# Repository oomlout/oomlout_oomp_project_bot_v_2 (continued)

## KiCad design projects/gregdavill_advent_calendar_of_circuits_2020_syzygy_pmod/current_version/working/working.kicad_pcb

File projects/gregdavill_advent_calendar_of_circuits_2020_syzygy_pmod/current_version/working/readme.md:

# advent_calendar_of_circuits_2020
 
## summary 
* id: gregdavill_advent_calendar_of_circuits_2020_syzygy_pmod
* user: gregdavill
* name: advent_calendar_of_circuits_2020
* board: syzygy_pmod
* repo: https://github.com/gregdavill/advent-calendar-of-circuits-2020
* src_file_repo_kicad_pcb: syzygy-pmod/kicad-src/syzygy-pmod.kicad_pcb
* src_file_repo_kicad_pcb_link: https://github.com/gregdavill/advent-calendar-of-circuits-2020/tree/main/syzygy-pmod/kicad-src/syzygy-pmod.kicad_pcb
* src_file_repo_kicad_sch: syzygy-pmod/kicad-src/p-mcu.kicad_sch
* src_file_repo_kicad_sch_link: https://github.com/gregdavill/advent-calendar-of-circuits-2020/tree/main/syzygy-pmod/kicad-src/p-mcu.kicad_sch

* src_file_repo_sch: 
* src_file_repo_sch_link: https://github.com/gregdavill/advent-calendar-of-circuits-2020/tree/main/
* full details link: https://github.com/oomlout/oomlout_oomp_project_bot_v_2/tree/main/projects/gregdavill_advent_calendar_of_circuits_2020_syzygy_pmod/current_version/working

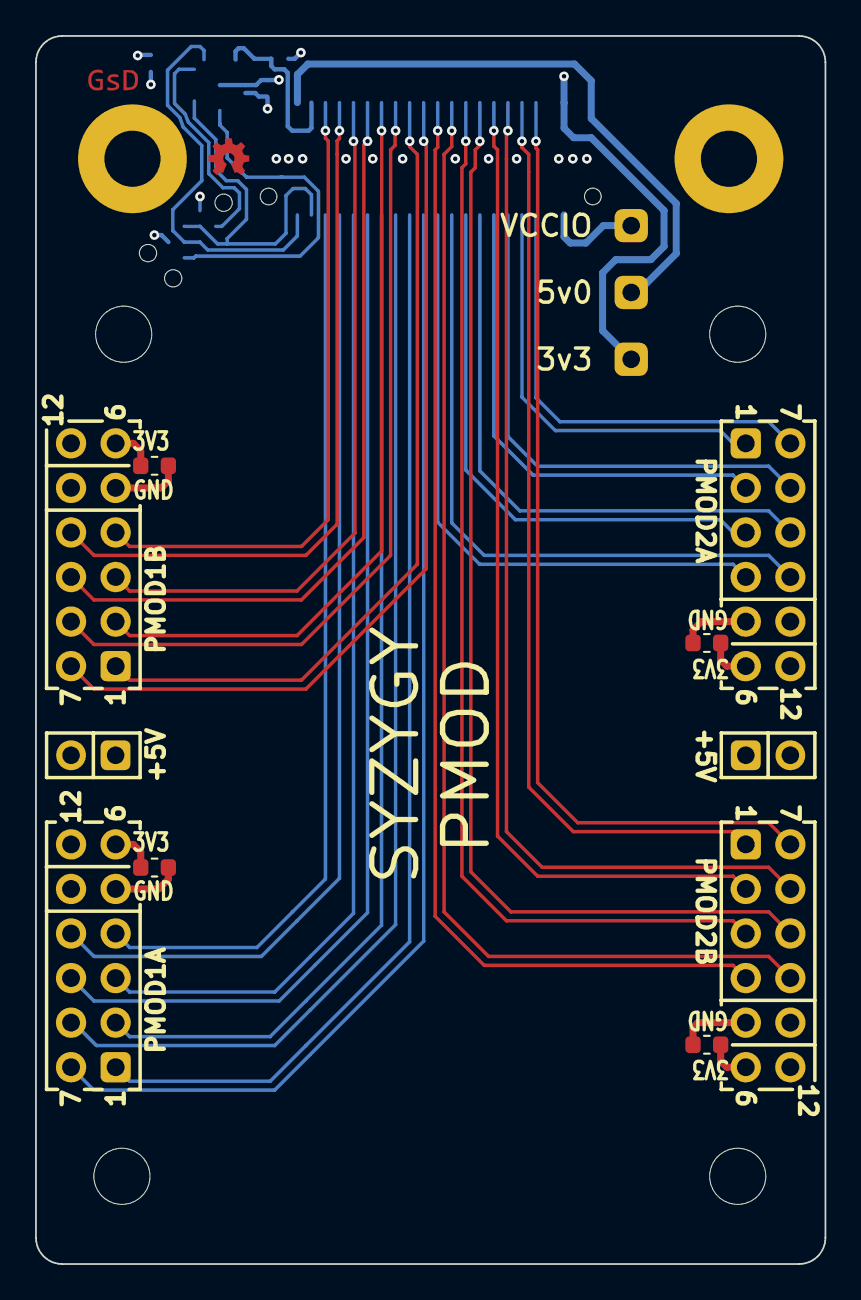
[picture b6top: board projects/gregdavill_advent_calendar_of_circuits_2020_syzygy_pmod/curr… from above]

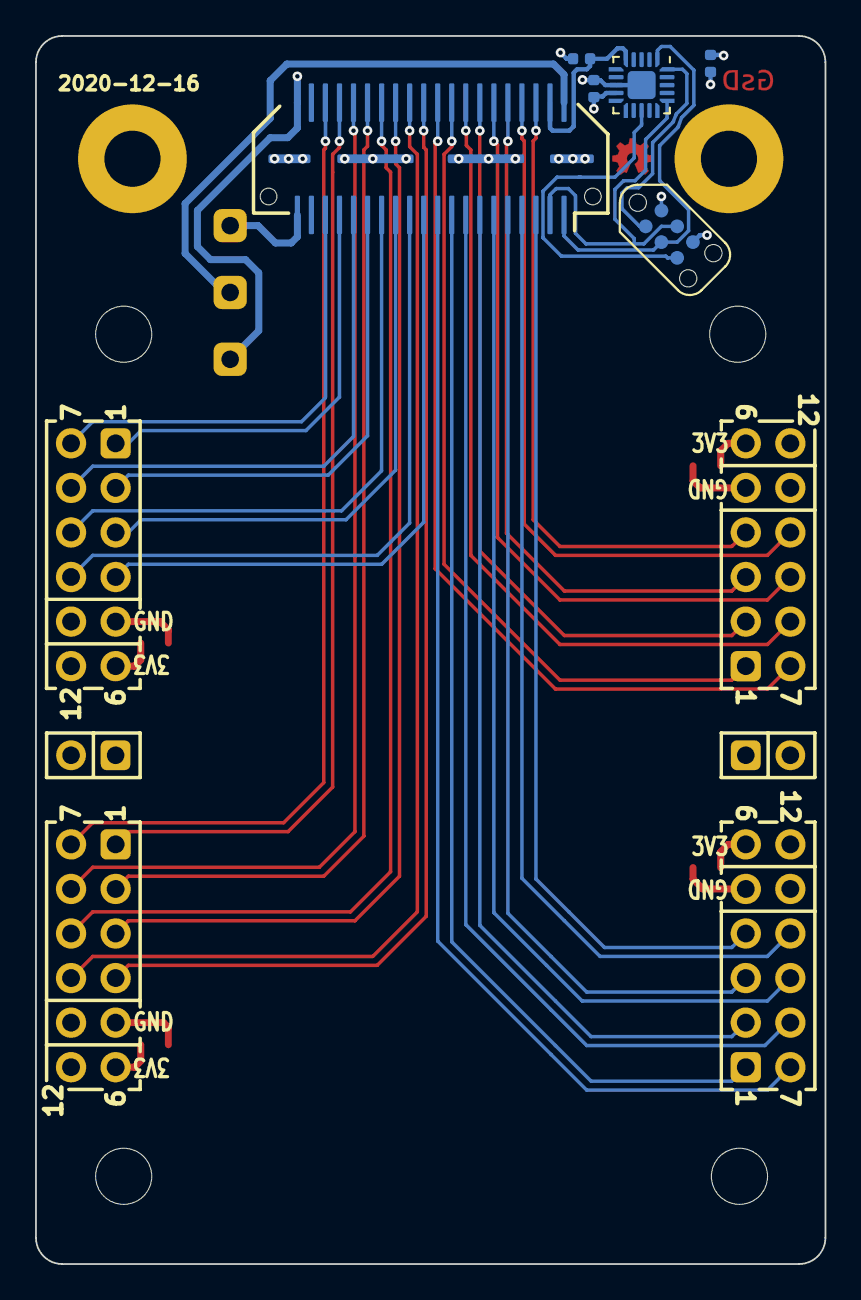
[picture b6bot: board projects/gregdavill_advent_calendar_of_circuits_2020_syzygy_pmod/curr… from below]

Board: 4 copper layers, 45.0 x 70.0 mm, 23 parts (6 on the bottom side), 41 nets.

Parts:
C1, C2, C3, C4: DNP; C_0603_1608Metric
C9: 0.1uF; C_0402_1005Metric
C10: 1uF; C_0402_1005Metric
H1, H2, H3, H4: MountingHole; MountingHole_3.2mm_M3_DIN965
J1: SYZYGY-STD; SYZYGY-STD-POD
J2, J8, J9, J11: PMOD; PMOD_Angled_2x06
J3: TagConnect; TC2030-NL_SMALL
J4, J5, J6: Conn_01x01_Male; PinHeader_1x01_P2.54mm_Vertical
J7, J10: 5V AUX; PinHeader_2x01_P2.54mm_Vertical
R15: 10K; R_0402_1005Metric
U2: ATtiny44A-MMH; QFN-20-1EP_3x3mm_P0.45mm_EP1.6x1.6mm

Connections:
+3V3: C1.2, C2.2, C3.2, C4.2, C9.1, C10.1, J1.40 (+3.3V), J2.6, J2.12, J3.2, J5.1, J8.6, J8.12, J9.6, J9.12, J11.6, J11.12, R15.1, U2.9 (VCC)
+5V: J1.2 (+5V), J4.1, J7.1, J10.1
/P1A1: J1.17 (S12_D6P), J9.1
/P1A2: J1.13 (S8_D4P), J9.2
/P1A3: J1.9 (S4_D2P), J9.3
/P1A4: J1.5 (S0_D0P), J9.4
/P1A7: J1.19 (S14_D6N), J9.7
/P1A8: J1.15 (S10_D4N), J9.8
/P1A9: J1.11 (S6_D2N), J9.9
/P1A10: J1.7 (S2_D0N), J9.10
/P1B1: J1.18 (S13_D7P), J11.1
/P1B2: J1.14 (S9_D5P), J11.2
/P1B3: J1.10 (S5_D3P), J11.3
/P1B4: J1.6 (S1_D1P), J11.4
/P1B7: J1.20 (S15_D7N), J11.7
/P1B8: J1.16 (S11_D5N), J11.8
/P1B9: J1.12 (S7_D3N), J11.9
/P1B10: J1.8 (S3_D1N), J11.10
/P2A1: J1.33 (P2C_CLKP), J2.1
/P2A2: J1.29 (S24), J2.2
/P2A3: J1.25 (S20), J2.3
/P2A4: J1.21 (S16), J2.4
/P2A7: J1.35 (P2C_CLKN), J2.7
/P2A8: J1.31 (S26), J2.8
/P2A9: J1.27 (S22), J2.9
/P2A10: J1.23 (S18), J2.10
/P2B1: J1.34 (C2P_CLKP), J8.1
/P2B2: J1.30 (S25), J8.2
/P2B3: J1.26 (S21), J8.3
/P2B4: J1.22 (S17), J8.4
/P2B7: J1.36 (C2P_CLKN), J8.7
/P2B8: J1.32 (S27), J8.8
/P2B9: J1.28 (S23), J8.9
/P2B10: J1.24 (S19), J8.10
/Peripheral MCU/MISO: J3.1, U2.20 (PA5)
/Peripheral MCU/~RESET: J3.5, U2.13 (~RESET~/PB3)
/RGA: J1.4 (R_GA), R15.2, U2.5 (AREF/PA0)
/SCL: J1.1 (SCL), J3.3, U2.1 (PA4)
/SDA: J1.3 (SDA), J3.4, U2.16 (PA6)
/VCCIO: J1.39 (VIO1), J6.1
GND: C1.1, C2.1, C3.1, C4.1, C9.2, C10.2, J1.41 (GND), J2.5, J2.11, J3.6, J7.2, J8.5, J8.11, J9.5, J9.11, J10.2, J11.5, J11.11, U2.8 (GND), U2.21 (GND)

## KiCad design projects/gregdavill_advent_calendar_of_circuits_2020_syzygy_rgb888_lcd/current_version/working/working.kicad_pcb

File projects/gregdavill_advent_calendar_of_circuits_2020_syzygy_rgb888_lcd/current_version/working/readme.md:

# advent_calendar_of_circuits_2020
 
## summary 
* id: gregdavill_advent_calendar_of_circuits_2020_syzygy_rgb888_lcd
* user: gregdavill
* name: advent_calendar_of_circuits_2020
* board: syzygy_rgb888_lcd
* repo: https://github.com/gregdavill/advent-calendar-of-circuits-2020
* src_file_repo_kicad_pcb: syzygy-rgb888-lcd/kicad-src/syzygy-rgb888-lcd.kicad_pcb
* src_file_repo_kicad_pcb_link: https://github.com/gregdavill/advent-calendar-of-circuits-2020/tree/main/syzygy-rgb888-lcd/kicad-src/syzygy-rgb888-lcd.kicad_pcb
* src_file_repo_kicad_sch: syzygy-rgb888-lcd/kicad-src/p-mcu.kicad_sch
* src_file_repo_kicad_sch_link: https://github.com/gregdavill/advent-calendar-of-circuits-2020/tree/main/syzygy-rgb888-lcd/kicad-src/p-mcu.kicad_sch

* src_file_repo_sch: 
* src_file_repo_sch_link: https://github.com/gregdavill/advent-calendar-of-circuits-2020/tree/main/
* full details link: https://github.com/oomlout/oomlout_oomp_project_bot_v_2/tree/main/projects/gregdavill_advent_calendar_of_circuits_2020_syzygy_rgb888_lcd/current_version/working

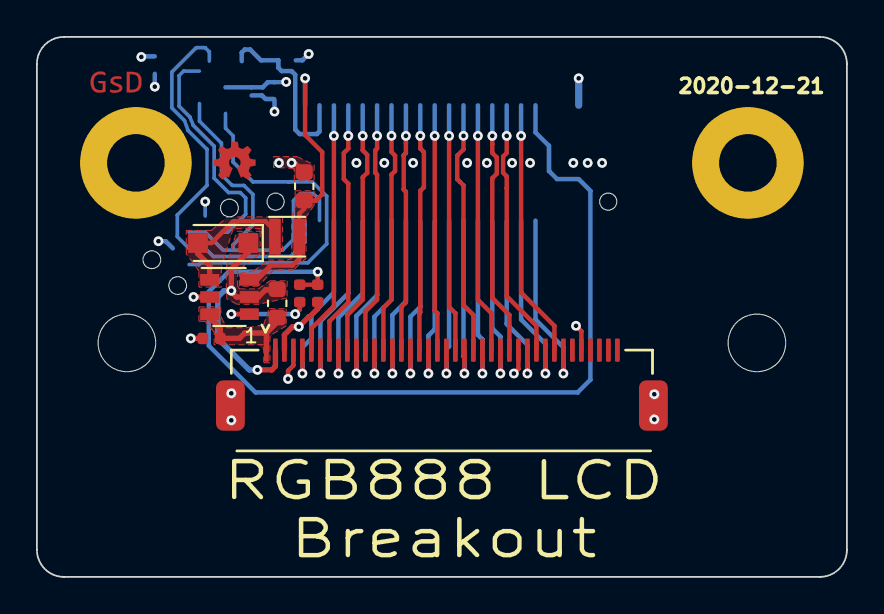
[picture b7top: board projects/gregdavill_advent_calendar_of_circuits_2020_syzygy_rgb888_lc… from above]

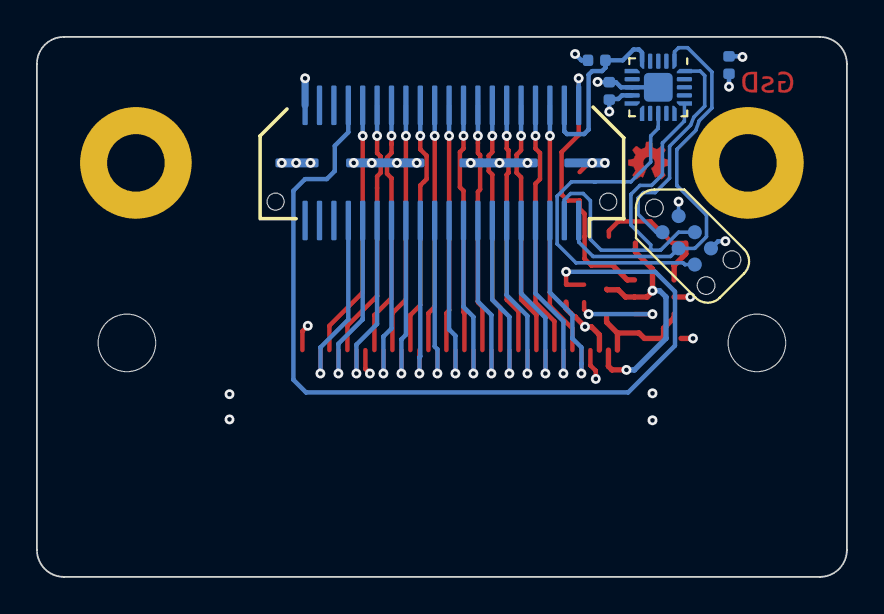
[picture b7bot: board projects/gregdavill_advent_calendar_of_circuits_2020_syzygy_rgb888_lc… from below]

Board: 4 copper layers, 45.0 x 30.0 mm, 17 parts (6 on the bottom side), 42 nets.

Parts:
C1: 0.1uF; C_0603_1608Metric
C2: 22uF; C_0603_1608Metric
C9: 0.1uF; C_0402_1005Metric
C10: 1uF; C_0402_1005Metric
D1: D_ALT; D_SOD-123F
H1, H2: MountingHole; MountingHole_3.2mm_M3_DIN965
J1: SYZYGY-STD; SYZYGY-STD-POD
J2: Conn_01x40_MountingPin; X05A20H40G
J3: TagConnect; TC2030-NL_SMALL
L1: 2.2uH; L_Taiyo-Yuden_MD-2020
R1: 1k; R_0402_1005Metric
R2: 10k; R_0402_1005Metric
R3: 5R1; R_0402_1005Metric
R15: 10K; R_0402_1005Metric
U1: PT4103; SOT-23-6
U2: ATtiny44A-MMH; QFN-20-1EP_3x3mm_P0.45mm_EP1.6x1.6mm

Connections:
+3V3: C9.1, C10.1, J1.40 (+3.3V), J2.4, J3.2, R15.1, U2.9 (VCC)
+5V: C2.1, J1.2 (+5V), L1.1, U1.6 (VIN)
/B0: J1.21 (S16), J2.21
/B1: J1.22 (S17), J2.22
/B2: J1.23 (S18), J2.23
/B3: J1.24 (S19), J2.24
/B4: J1.25 (S20), J2.25
/B5: J1.26 (S21), J2.26
/B6: J1.27 (S22), J2.27
/B7: J1.28 (S23), J2.28
/BLEN: J1.34 (C2P_CLKP), R1.1, R2.2
/CLK: J1.29 (S24), J2.30
/DEN: J1.33 (P2C_CLKP), J2.34
/DISP: J1.30 (S25), J2.31
/G0: J1.13 (S8_D4P), J2.13
/G1: J1.14 (S9_D5P), J2.14
/G2: J1.15 (S10_D4N), J2.15
/G3: J1.16 (S11_D5N), J2.16
/G4: J1.17 (S12_D6P), J2.17
/G5: J1.18 (S13_D7P), J2.18
/G6: J1.19 (S14_D6N), J2.19
/G7: J1.20 (S15_D7N), J2.20
/HSYNC: J1.31 (S26), J2.32
/Peripheral MCU/MISO: J3.1, U2.20 (PA5)
/Peripheral MCU/~RESET: J3.5, U2.13 (~RESET~/PB3)
/R0: J1.5 (S0_D0P), J2.5
/R1: J1.6 (S1_D1P), J2.6
/R2: J1.7 (S2_D0N), J2.7
/R3: J1.8 (S3_D1N), J2.8
/R4: J1.9 (S4_D2P), J2.9
/R5: J1.10 (S5_D3P), J2.10
/R6: J1.11 (S6_D2N), J2.11
/R7: J1.12 (S7_D3N), J2.12
/RGA: J1.4 (R_GA), R15.2, U2.5 (AREF/PA0)
/SCL: J1.1 (SCL), J3.3, U2.1 (PA4)
/SDA: J1.3 (SDA), J3.4, U2.16 (PA6)
/VLED+: C1.1, D1.1 (K), J2.2, U1.5 (OV)
/VLED-: C1.2, J2.1, R3.2, U1.3 (FB)
/VSYNC: J1.32 (S27), J2.33
GND: C2.2, C9.2, C10.2, J1.41 (GND), J2.3, J2.29, J2.36, J2.MP (MountPin), J3.6, R2.1, R3.1, U1.2 (GND), U2.8 (GND), U2.21 (GND)
unnamed: D1.2 (A), L1.2, U1.1 (LX)
unnamed: R1.2, U1.4 (EN)

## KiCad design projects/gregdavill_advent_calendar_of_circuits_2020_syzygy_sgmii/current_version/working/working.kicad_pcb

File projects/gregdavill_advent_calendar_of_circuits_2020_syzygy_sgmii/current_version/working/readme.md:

# advent_calendar_of_circuits_2020
 
## summary 
* id: gregdavill_advent_calendar_of_circuits_2020_syzygy_sgmii
* user: gregdavill
* name: advent_calendar_of_circuits_2020
* board: syzygy_sgmii
* repo: https://github.com/gregdavill/advent-calendar-of-circuits-2020
* src_file_repo_kicad_pcb: syzygy-sgmii/kicad-src/syzygy-sgmii.kicad_pcb
* src_file_repo_kicad_pcb_link: https://github.com/gregdavill/advent-calendar-of-circuits-2020/tree/main/syzygy-sgmii/kicad-src/syzygy-sgmii.kicad_pcb
* src_file_repo_kicad_sch: syzygy-sgmii/kicad-src/pMCU.kicad_sch
* src_file_repo_kicad_sch_link: https://github.com/gregdavill/advent-calendar-of-circuits-2020/tree/main/syzygy-sgmii/kicad-src/pMCU.kicad_sch

* src_file_repo_sch: 
* src_file_repo_sch_link: https://github.com/gregdavill/advent-calendar-of-circuits-2020/tree/main/
* full details link: https://github.com/oomlout/oomlout_oomp_project_bot_v_2/tree/main/projects/gregdavill_advent_calendar_of_circuits_2020_syzygy_sgmii/current_version/working

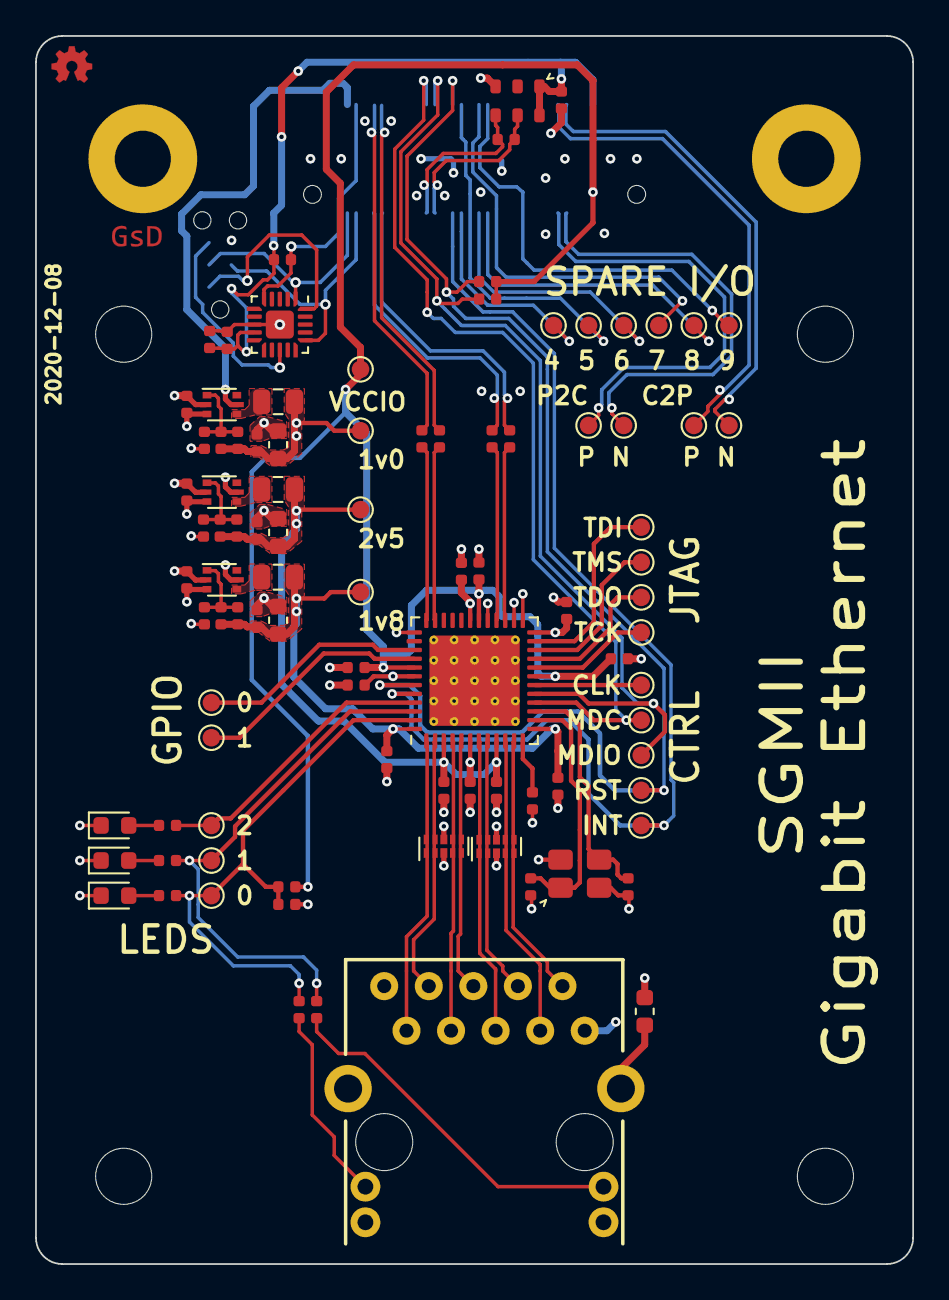
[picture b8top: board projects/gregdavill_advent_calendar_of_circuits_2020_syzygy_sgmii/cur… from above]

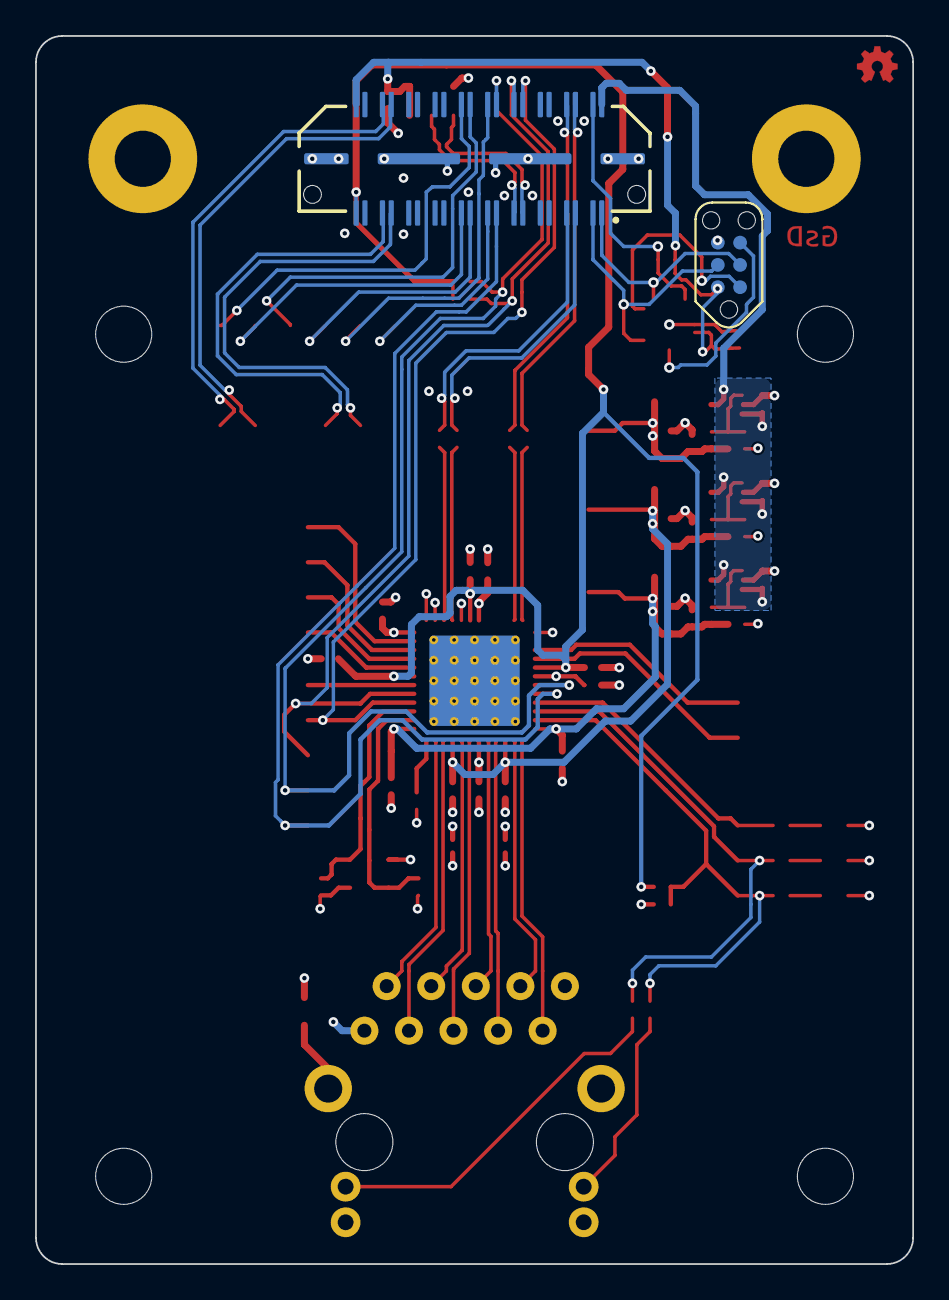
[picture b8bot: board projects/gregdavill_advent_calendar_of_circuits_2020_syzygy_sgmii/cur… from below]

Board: 4 copper layers, 50.0 x 70.0 mm, 101 parts (2 on the bottom side), 69 nets.

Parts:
C1, C2, C6, C7, C9, C21, C22, C23, C24, C25, C26, C27, C28, C29, C30, C31, C32: 0.1uF; C_0402_1005Metric
C3, C4: 10pF; C_0402_1005Metric
C5, C8, C11: 4.7uF; C_0402_1005Metric
C10, C18, C19, C20: 1uF; C_0402_1005Metric
C12, C13, C14: 6.8pF; C_0402_1005Metric
C15, C16, C17: 10uF; C_0603_1608Metric
CON1: JD1_0001NL; JD1-0001NL
D1, D2, D3: LED_ALT; LED_0603_1608Metric
FB1: 100R; L_0603_1608Metric
H1, H2, H3, H4: MountingHole; MountingHole_3.2mm_M3
J1: SYZYGY-TXR-4; SYZYGY-TXR-POD
J3: TagConnect; TC2030-NL_SMALL
L1, L2, L3: 2.2uH; L_0805_2012Metric
R1: 11K; R_0402_1005Metric
R2, R7, R15: 10K; R_0402_1005Metric
R3, R5: 15K; R_0402_1005Metric
R4: 47.5K; R_0402_1005Metric
R6: 20K; R_0402_1005Metric
R8, R9, R10, R11, R12, R13, R14: 1.5K; R_0402_1005Metric
R16: 100R; R_0402_1005Metric
R17: 10k; R_0402_1005Metric
R18: 2.49k; R_0402_1005Metric
TP1, TP2, TP3, TP4, TP6, TP7, TP8, TP9, TP10, TP11, TP12, TP13, TP14, TP15, TP16, TP17, TP18, TP19, TP20, TP21, TP22, TP23, TP24, TP25, TP26, TP27, TP28, TP29: TestPoint_Alt; TestPoint_Pad_D1.0mm
U1: DP83867C; QFN-48-1EP_7x7mm_P0.5mm_EP5.15x5.15mm_ThermalVias
U2: ATtiny44A-MMH; QFN-20-1EP_3x3mm_P0.45mm_EP1.6x1.6mm
U3, U4, U5: TLV62569DRL; SOT-666
U6, U7: TPD4EUSB30; USON-10_2.5x1.0mm_P0.5mm
X1: SG3225VAN; Oscillator_SMD_Silicon_Labs_LGA-6_2.5x3.2mm_P1.25mm
Y1: 25MHz; Crystal_SMD_SeikoEpson_TSX3225-4Pin_3.2x2.5mm

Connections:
+1V0: C12.1, C15.1, C18.1, C28.1, C29.1, C30.1, C31.1, L1.2, R2.2, TP18.1, U1.6 (VDD1P0[4]), U1.24 (VDD1P0[4]), U1.31 (VDD1P0[4]), U1.42 (VDD1P0[4])
+1V8: C14.1, C17.1, C20.1, C26.1, C27.1, L3.2, R6.2, TP29.1, U1.13 (VDDA1P8[2]), U1.48 (VDDA1P8[2])
+2V5: C13.1, C16.1, C19.1, C24.1, C25.1, L2.2, R4.2, TP28.1, U1.3 (VDDA2P5[2]), U1.9 (VDDA2P5[2])
+3V3: C9.1, C10.1, C32.1, J1.40 (+3.3V), J3.2, R15.1, U2.9 (VCC), X1.1 (OE), X1.6 (Vcc)
+5V: C5.1, C8.1, C11.1, J1.2 (+5V), U3.3 (VIN), U3.5 (EN), U4.3 (VIN), U4.5 (EN), U5.3 (VIN), U5.5 (EN)
/C2P_CLK_N: J1.36 (C2P_CLKN), TP22.1
/C2P_CLK_P: J1.34 (C2P_CLKP), TP21.1
/CLK_OUT: TP13.1, U1.18 (CLK_OUT)
/ETH_A_N: CON1.9 (P8), U1.2 (TD_M_A), U6.2 (D1-)
/ETH_A_P: CON1.10 (P9), U1.1 (TD_P_A), U6.1 (D1+)
/ETH_B_N: CON1.7 (P6), U1.5 (TD_M_B), U6.5 (D2-)
/ETH_B_P: CON1.8 (P7), U1.4 (TD_P_B), U6.4 (D2+)
/ETH_C_N: CON1.5 (P4), U1.8 (TD_M_C), U7.2 (D1-)
/ETH_C_P: CON1.6 (P5), U1.7 (TD_P_C), U7.1 (D1+)
/ETH_D_N: CON1.3 (P2), U1.11 (TD_M_D), U7.5 (D2-)
/ETH_D_P: CON1.4 (P3), U1.10 (TD_P_D), U7.4 (D2+)
/GPIO0: TP23.1, U1.39 (GPIO_0)
/GPIO1: TP24.1, U1.40 (GPIO_1)
/INT/PWDN: J1.17 (S2), TP12.1, U1.44 (INT/PWDN)
/JTAG_CLK: TP14.1, U1.20 (JTAG_CLK)
/JTAG_TDI: TP15.1, U1.23 (JTAG_TDI)
/JTAG_TDO: TP16.1, U1.21 (JTAG_TDO)
/JTAG_TMS: TP17.1, U1.22 (JTAG_TMS)
/LED0: R10.1, R12.1, R17.1, R18.1, TP25.1, U1.47 (LED_0)
/LED1: R11.1, R13.1, TP26.1, U1.46 (LED_1)
/LED2: R14.1, TP27.1, U1.45 (LED_2)
/MDC: J1.14 (S0), TP9.1, U1.16 (MDC)
/MDIO: J1.16 (S1), R8.2, TP10.1, U1.17 (MDIO)
/P2C_CLK_N: J1.35 (P2C_CLKN), TP20.1
/P2C_CLK_P: J1.33 (P2C_CLKP), TP19.1
/Peripheral MCU/MISO: J3.1, U2.20 (PA5)
/Peripheral MCU/~RESET: J3.5, U2.13 (~RESET~/PB3)
/REFCLK_N: J1.15 (REFCLKN), R16.1, X1.5 (~OUT)
/REFCLK_P: J1.13 (REFCLKP), R16.2, X1.4 (OUT)
/RESET_N: J1.18 (S3), R9.2, TP11.1, U1.43 (RESET_N)
/RGA: J1.4 (R_GA), R15.2, U2.5 (AREF/PA0)
/S4: J1.19 (S4), TP2.1
/S5: J1.20 (S5), TP6.1
/S6: J1.21 (S6), TP3.1
/S7: J1.22 (S7), TP7.1
/S8: J1.23 (S8), TP4.1
/S9: J1.24 (S9), TP8.1
/SCL: J1.1 (SCL), J3.3, U2.1 (PA4)
/SDA: J1.3 (SDA), J3.4, U2.16 (PA6)
/SGMII_SI_N: C1.2, U1.28 (TX_D0/SGMII_SIN)
/SGMII_SI_P: C6.2, U1.27 (TX_D1/SGMII_SIP)
/SGMII_SO_N: C7.2, U1.36 (RX_D3/SGMII_SON)
/SGMII_SO_P: C2.2, U1.35 (RX_D2/SGMII_SOP)
/VCCIO: C21.1, C22.1, C23.1, J1.39 (VIO1), R8.1, R9.1, R17.2, TP1.1, U1.19 (VDDIO[3]), U1.30 (VDDIO[3]), U1.41 (VDDIO[3])
/_SGMII_SI_N: C1.1, J1.5 (RX0P)
/_SGMII_SI_P: C6.1, J1.7 (RX0N)
/_SGMII_SO_N: C7.1, J1.6 (TX0P)
/_SGMII_SO_P: C2.1, J1.8 (TX0N)
GND: C3.2, C4.2, C5.2, C8.2, C9.2, C10.2, C11.2, C15.2, C16.2, C17.2, C18.2, C19.2, C20.2, C21.2, C22.2, C23.2, C24.2, C25.2, C26.2, C27.2, C28.2, C29.2, C30.2, C31.2, C32.2, CON1.2 (P1), CON1.13 (GREEN_K), CON1.15 (YELLOW_K), D1.1 (K), D2.1 (K), D3.1 (K), FB1.1, J1.41 (GND), J3.6, R1.1, R3.1, R5.1, R7.1, R18.2, U1.25 (TX_D3), U1.26 (TX_D2), U1.29 (GTX_CLK), U1.37 (TX_CTRL), U1.49 (GND), U2.8 (GND), U2.21 (GND), U3.2 (GND), U4.2 (GND), U5.2 (GND), U6.3 (GND), U7.3 (GND), X1.3 (GND), Y1.2, Y1.4
unnamed: C3.1, U1.14 (XO), Y1.1
unnamed: C4.1, U1.15 (XI), Y1.3
unnamed: C12.2, R2.1, R3.2, U3.1 (FB)
unnamed: C13.2, R4.1, R5.2, U4.1 (FB)
unnamed: C14.2, R6.1, R7.2, U5.1 (FB)
unnamed: CON1.1 (SHEILD), FB1.2
unnamed: CON1.12 (GREEN_A), R11.2
unnamed: CON1.14 (YELLOW_A), R10.2
unnamed: D1.2 (A), R12.2
unnamed: D2.2 (A), R13.2
unnamed: D3.2 (A), R14.2
unnamed: L1.1, U3.4 (SW)
unnamed: L2.1, U4.4 (SW)
unnamed: L3.1, U5.4 (SW)
unnamed: R1.2, U1.12 (RBIAS)
